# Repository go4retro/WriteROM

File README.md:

# WriteROM

WriteROM accomplishes the impossible, allowing one to write a ROM in place while installed in a circuit without a write line. No flying leads or pigtails are required. WriteROM allows writing to the FLASH using only read accesses.

In normal operation, WriteROM works just like a normal 28 pin JEDEC ROM. However, once a "knock" sequence of reads are performed on the device, the device enters into a programming mode, where address bits 7-0 are interpreted as the data, and bits 11-8 are considered the "operation". The following operations are supported:

| 10:8 | Description                |
| ---- | -------------------------- |
| 0    | set low byte of address    |
| 1    | set middle byte of address |
| 2    | set high byte of address   |
| 6    | read from stored address   |
| 7    | write to address           |

As expected, programming times will be increased due to the additional level of abstraction, but such a device can be cleanly inserted into any memory map, even those not allowing writes to a specific range of memory.

Currently, the design includes a 4Mbit (512kB) FLASH ROM, though the design can be extended to larger sizes if desired.

## License

Copyright (C) 2025 RETRO Innovations

These files are free designs; you can redistribute them and/or modify
them under the terms of the Creative Commons Attribution-ShareAlike 
4.0 International License.

You should have received a copy of the license along with this
work. If not, see http://creativecommons.org/licenses/by-sa/4.0/.

These files are distributed in the hope that they will be useful,
but WITHOUT ANY WARRANTY; without even the implied warranty of
MERCHANTABILITY or FITNESS FOR A PARTICULAR PURPOSE. See the
license for more details.

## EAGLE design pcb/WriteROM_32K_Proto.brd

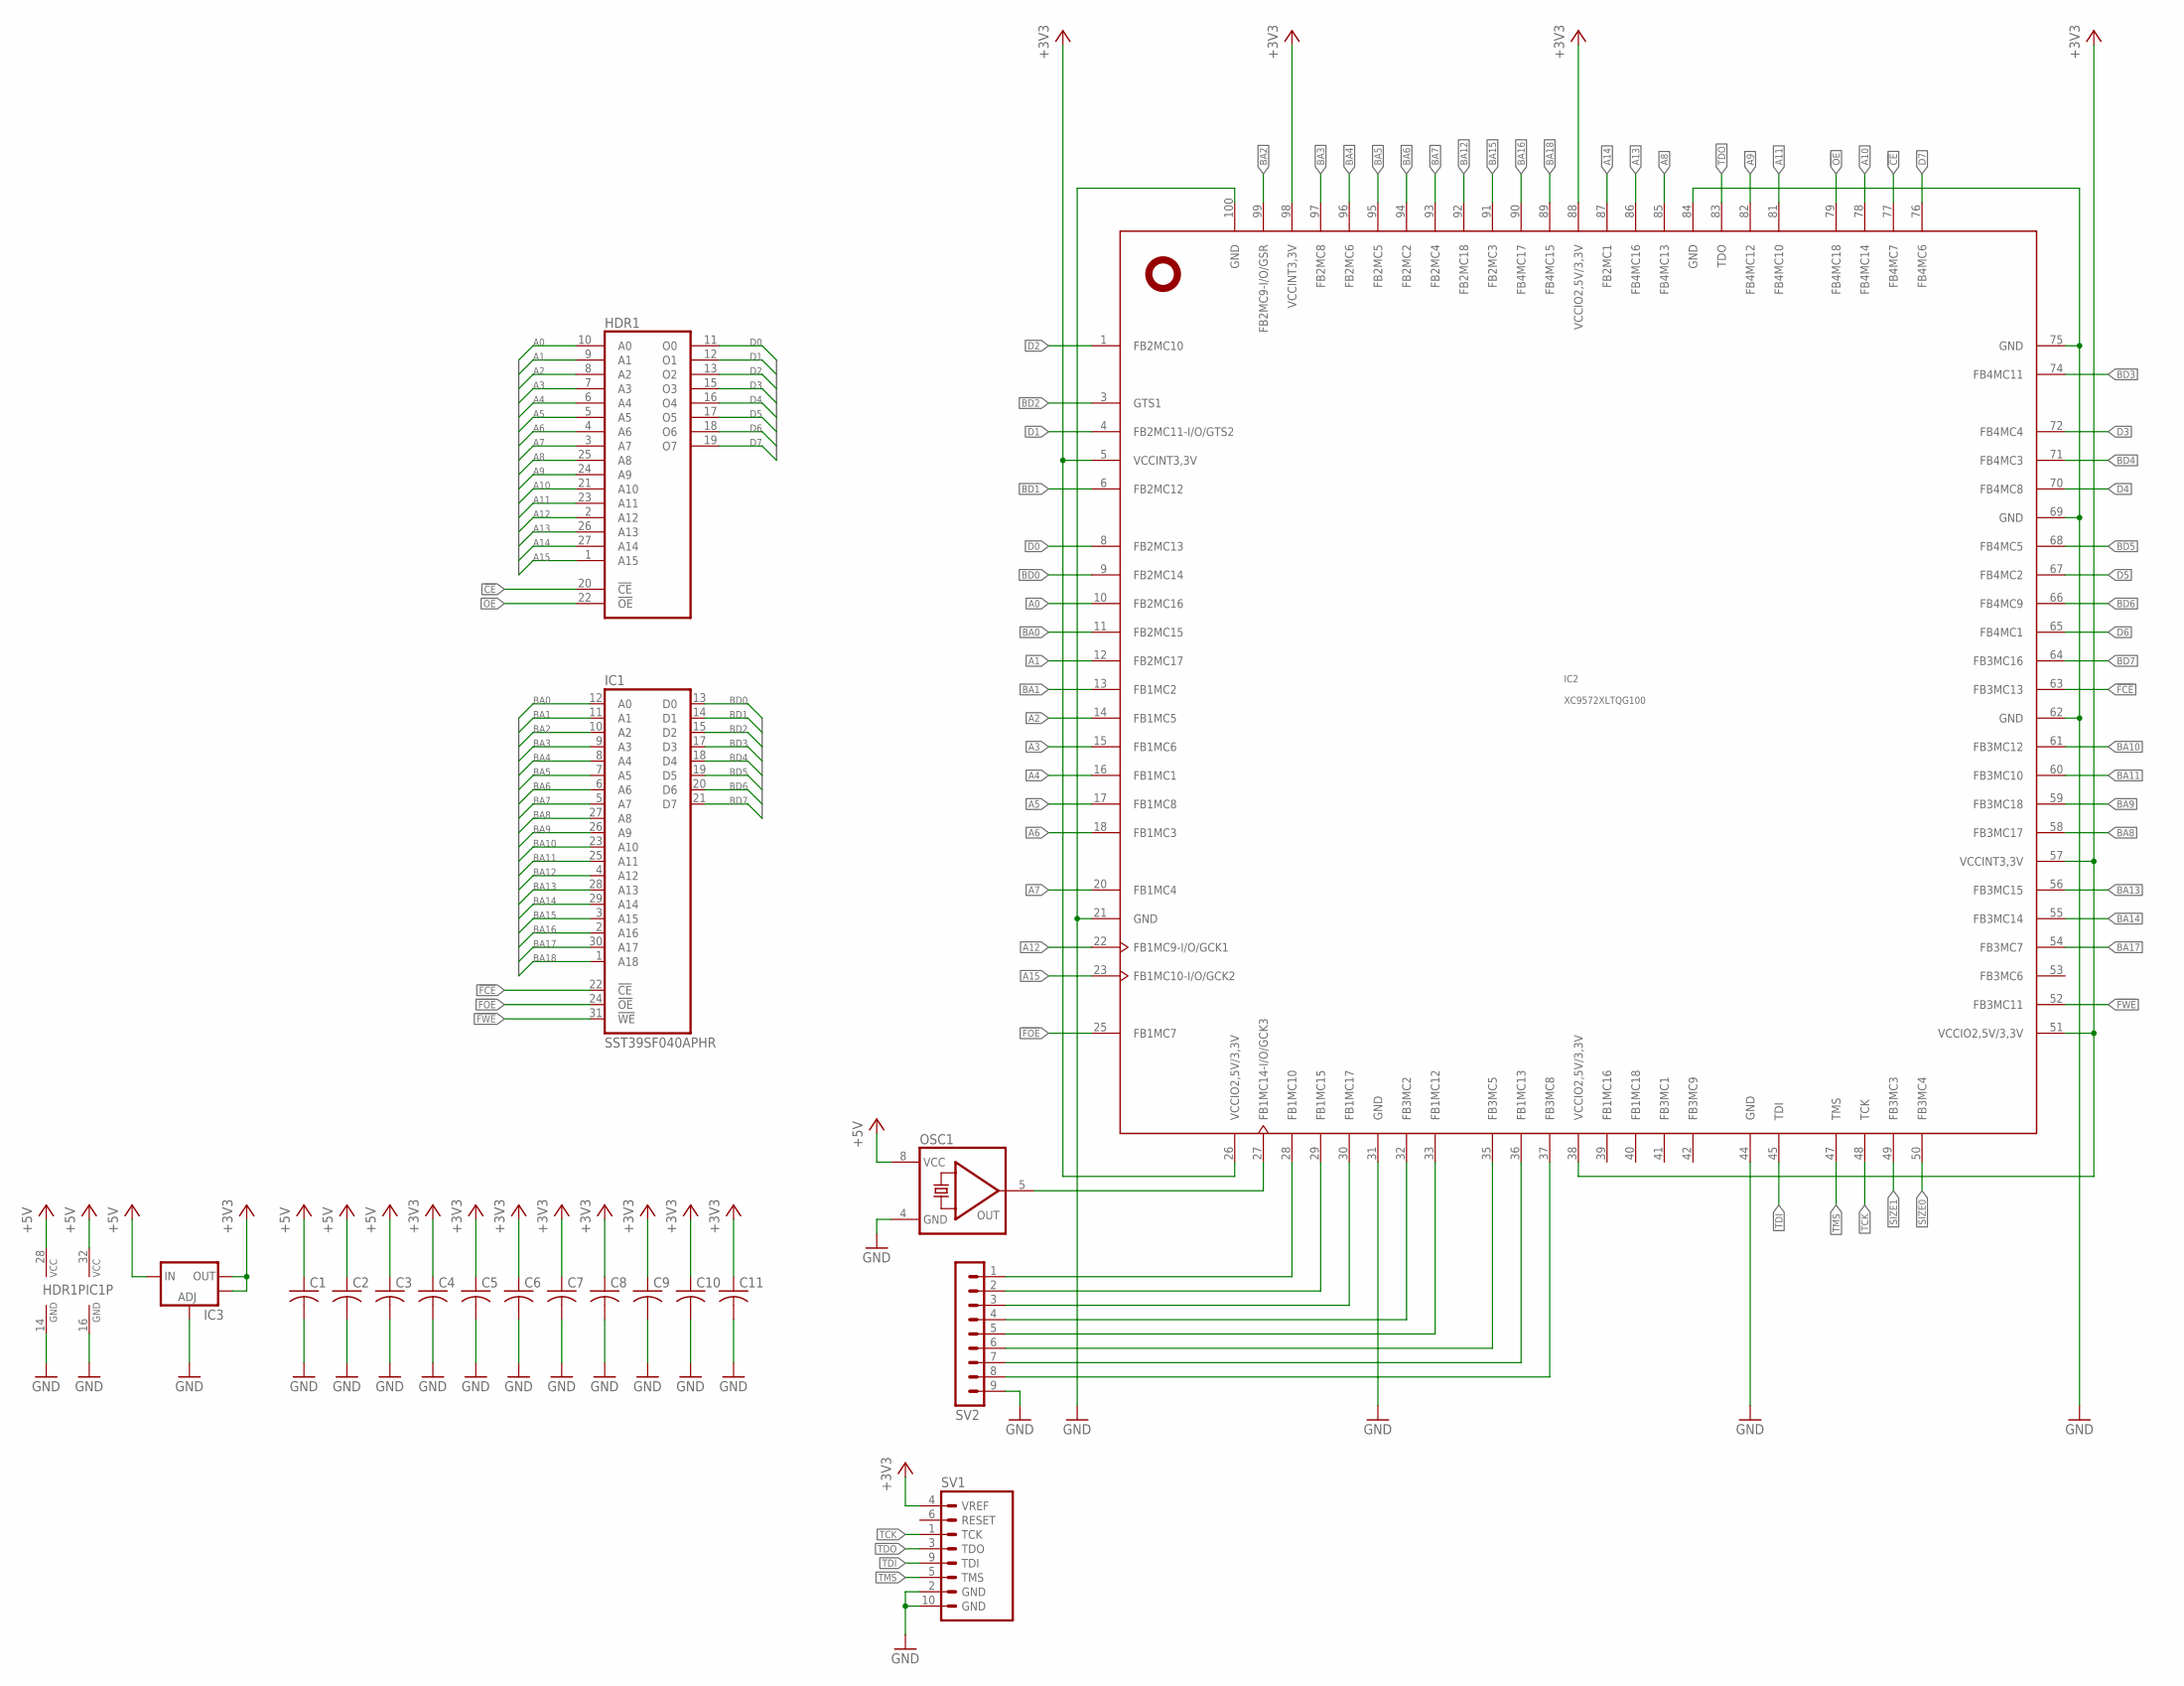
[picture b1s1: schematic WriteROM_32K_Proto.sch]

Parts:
C1, C4: C-USC0805; C0805
C2, C3, C5, C6, C7, C8, C9, C10, C11: C-USC0402; C0402
HDR1: 27512; DIL28
IC1: SST39SF040APHR; DIL32-RP
IC2: XC9572XLTQG100; TQFP100
IC3: V_REG_LM1117SOT223; SOT223
OSC1: QG5460; DIL08S
SV1: JTAG
SV2: MA09-1

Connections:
!CE: HDR1.20 (!CE), IC2.77 (FB4MC7)
!FCE: IC1.22 (!CE), IC2.63 (FB3MC13)
!FOE: IC1.24 (!OE), IC2.25 (FB1MC7)
!FWE: IC1.31 (!WE), IC2.52 (FB3MC11)
!OE: HDR1.22 (!OE), IC2.79 (FB4MC18)
+3V3: C4.1, C5.1, C6.1, C7.1, C8.1, C9.1, C10.1, C11.1, IC2.5 (VCCINT3,3V), IC2.26 (VCCIO2,5V/3,3V), IC2.38 (VCCIO2,5V/3,3V), IC2.51 (VCCIO2,5V/3,3V), IC2.57 (VCCINT3,3V), IC2.88 (VCCIO2,5V/3,3V), IC2.98 (VCCINT3,3V), IC3.2 (OUT), IC3.4 (OUT), SV1.4 (VREF)
+5V: C1.1, C2.1, C3.1, HDR1.28 (VCC), IC1.32 (VCC), IC3.3 (IN), OSC1.8 (VCC)
A0: HDR1.10 (A0), IC2.10 (FB2MC16)
A1: HDR1.9 (A1), IC2.12 (FB2MC17)
A2: HDR1.8 (A2), IC2.14 (FB1MC5)
A3: HDR1.7 (A3), IC2.15 (FB1MC6)
A4: HDR1.6 (A4), IC2.16 (FB1MC1)
A5: HDR1.5 (A5), IC2.17 (FB1MC8)
A6: HDR1.4 (A6), IC2.18 (FB1MC3)
A7: HDR1.3 (A7), IC2.20 (FB1MC4)
A8: HDR1.25 (A8), IC2.85 (FB4MC13)
A9: HDR1.24 (A9), IC2.82 (FB4MC12)
A10: HDR1.21 (A10), IC2.78 (FB4MC14)
A11: HDR1.23 (A11), IC2.81 (FB4MC10)
A12: HDR1.2 (A12), IC2.22 (FB1MC9-I/O/GCK1)
A13: HDR1.26 (A13), IC2.86 (FB4MC16)
A14: HDR1.27 (A14), IC2.87 (FB2MC1)
A15: HDR1.1 (A15), IC2.23 (FB1MC10-I/O/GCK2)
BA0: IC1.12 (A0), IC2.11 (FB2MC15)
BA1: IC1.11 (A1), IC2.13 (FB1MC2)
BA2: IC1.10 (A2), IC2.99 (FB2MC9-I/O/GSR)
BA3: IC1.9 (A3), IC2.97 (FB2MC8)
BA4: IC1.8 (A4), IC2.96 (FB2MC6)
BA5: IC1.7 (A5), IC2.95 (FB2MC5)
BA6: IC1.6 (A6), IC2.94 (FB2MC2)
BA7: IC1.5 (A7), IC2.93 (FB2MC4)
BA8: IC1.27 (A8), IC2.58 (FB3MC17)
BA9: IC1.26 (A9), IC2.59 (FB3MC18)
BA10: IC1.23 (A10), IC2.61 (FB3MC12)
BA11: IC1.25 (A11), IC2.60 (FB3MC10)
BA12: IC1.4 (A12), IC2.92 (FB2MC18)
BA13: IC1.28 (A13), IC2.56 (FB3MC15)
BA14: IC1.29 (A14), IC2.55 (FB3MC14)
BA15: IC1.3 (A15), IC2.91 (FB2MC3)
BA16: IC1.2 (A16), IC2.90 (FB4MC17)
BA17: IC1.30 (A17), IC2.54 (FB3MC7)
BA18: IC1.1 (A18), IC2.89 (FB4MC15)
BD0: IC1.13 (D0), IC2.9 (FB2MC14)
BD1: IC1.14 (D1), IC2.6 (FB2MC12)
BD2: IC1.15 (D2), IC2.3 (GTS1)
BD3: IC1.17 (D3), IC2.74 (FB4MC11)
BD4: IC1.18 (D4), IC2.71 (FB4MC3)
BD5: IC1.19 (D5), IC2.68 (FB4MC5)
BD6: IC1.20 (D6), IC2.66 (FB4MC9)
BD7: IC1.21 (D7), IC2.64 (FB3MC16)
D0: HDR1.11 (O0), IC2.8 (FB2MC13)
D1: HDR1.12 (O1), IC2.4 (FB2MC11-I/O/GTS2)
D2: HDR1.13 (O2), IC2.1 (FB2MC10)
D3: HDR1.15 (O3), IC2.72 (FB4MC4)
D4: HDR1.16 (O4), IC2.70 (FB4MC8)
D5: HDR1.17 (O5), IC2.67 (FB4MC2)
D6: HDR1.18 (O6), IC2.65 (FB4MC1)
D7: HDR1.19 (O7), IC2.76 (FB4MC6)
GND: C1.2, C2.2, C3.2, C4.2, C5.2, C6.2, C7.2, C8.2, C9.2, C10.2, C11.2, HDR1.14 (GND), IC1.16 (GND), IC2.21 (GND), IC2.31 (GND), IC2.44 (GND), IC2.62 (GND), IC2.69 (GND), IC2.75 (GND), IC2.84 (GND), IC2.100 (GND), IC3.1 (ADJ), OSC1.4 (GND), SV1.2 (GND), SV1.10 (GND), SV2.9
unnamed: IC2.27 (FB1MC14-I/O/GCK3), OSC1.5 (OUT)
SIZE0: IC2.50 (FB3MC4)
SIZE1: IC2.49 (FB3MC3)
TCK: IC2.48 (TCK), SV1.1 (TCK)
TDI: IC2.45 (TDI), SV1.9 (TDI)
TDO: IC2.83 (TDO), SV1.3 (TDO)
TES2: IC2.30 (FB1MC17), SV2.3
TEST0: IC2.28 (FB1MC10), SV2.1
TEST1: IC2.29 (FB1MC15), SV2.2
TEST3: IC2.32 (FB3MC2), SV2.4
TEST4: IC2.33 (FB1MC12), SV2.5
TEST5: IC2.35 (FB3MC5), SV2.6
TEST6: IC2.36 (FB1MC13), SV2.7
TEST7: IC2.37 (FB3MC8), SV2.8
TMS: IC2.47 (TMS), SV1.5 (TMS)

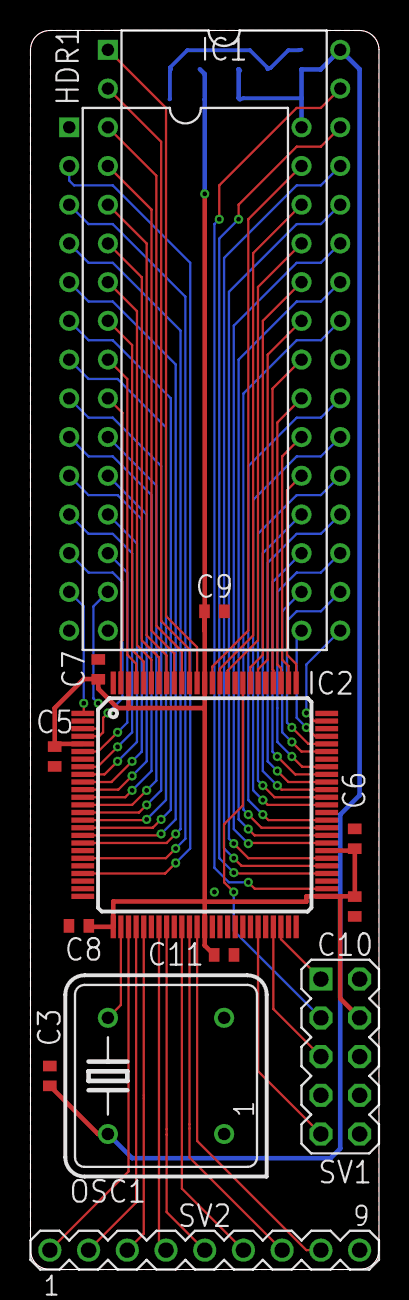
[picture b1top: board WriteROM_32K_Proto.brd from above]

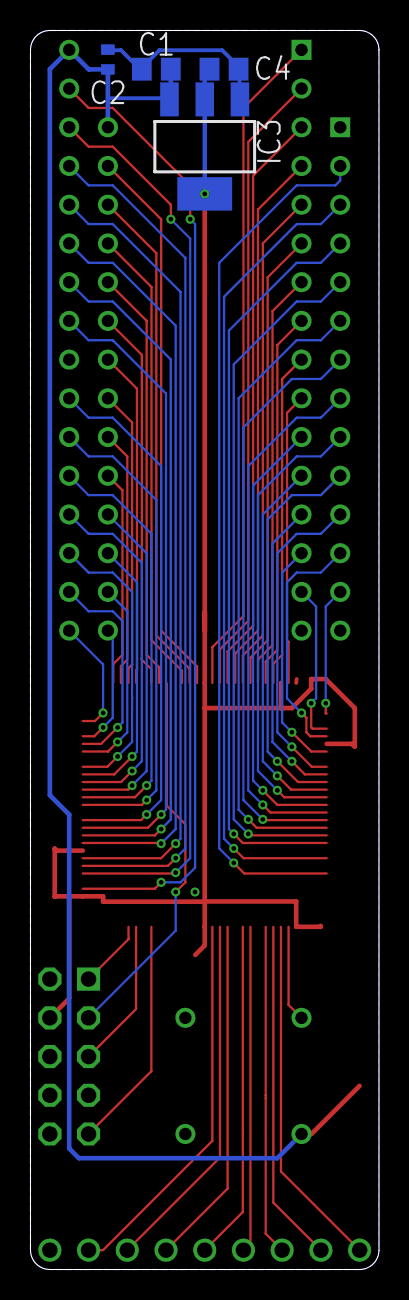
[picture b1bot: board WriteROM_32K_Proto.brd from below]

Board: 2 copper layers, 22.9 x 81.3 mm, 18 parts (4 on the bottom side), 72 nets.

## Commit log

2025-09-04 Remove secondary clock synchronization
2025-09-04 Fix issue with lock sequence changing address high byte
2025-09-05 Added more flexibility to banking
2025-09-05 Support CPUs that do "dead reads" on FFFF by ignoring those reads.

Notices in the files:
parts and their libraries:
SparkFun: Licensing: CC v3.0 Share-Alike You are welcome to use this library for commercial purposes.
